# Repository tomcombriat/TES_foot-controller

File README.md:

# TES foot controller

A foot controller performing MIDI looping and arpegiator.
Build instructions and comments will be added in a near future…

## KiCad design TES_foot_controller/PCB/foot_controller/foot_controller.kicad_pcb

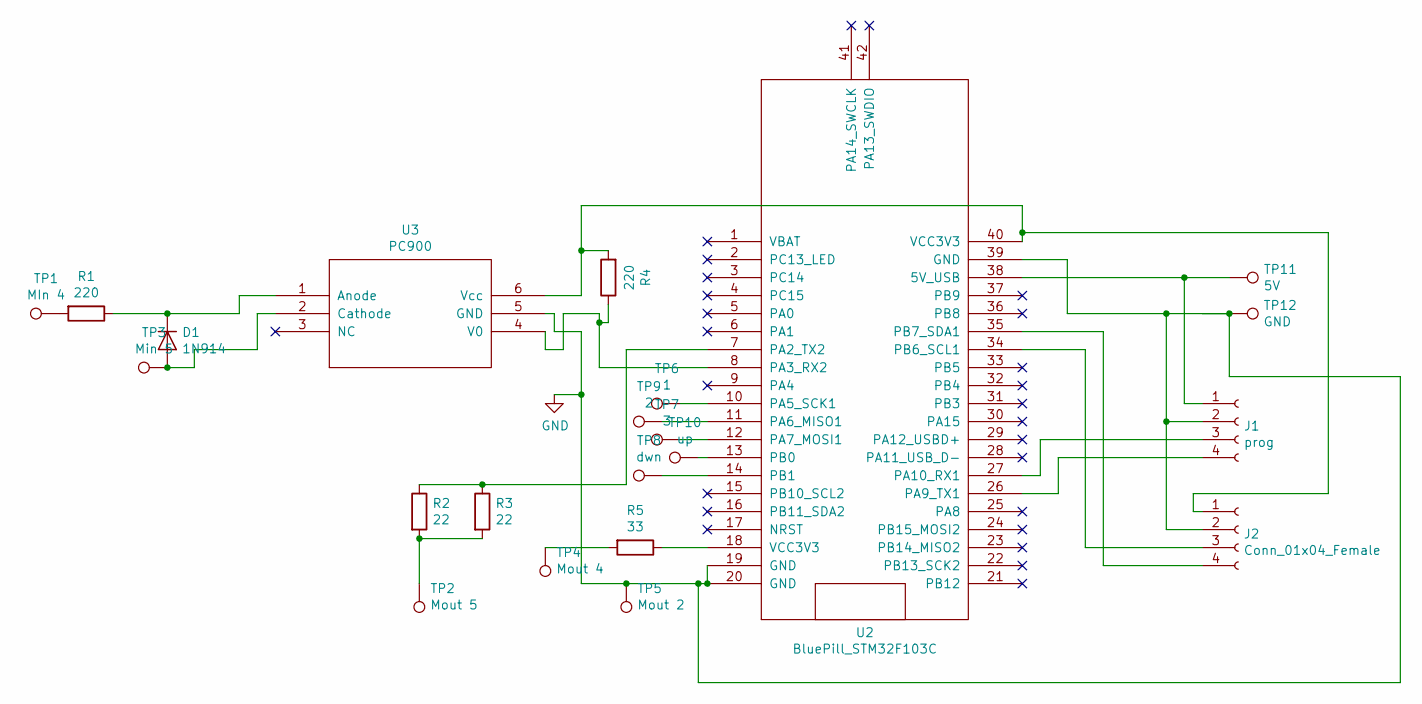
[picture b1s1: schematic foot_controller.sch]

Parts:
D1: 1N914; D_DO-35_SOD27_P7.62mm_Horizontal
J1: prog; PinHeader_1x04_P2.54mm_Vertical
J2: Conn_01x04_Female; PinHeader_1x04_P2.54mm_Vertical
R1, R4: 220; R_Axial_DIN0207_L6.3mm_D2.5mm_P7.62mm_Horizontal
R2, R3: 22; R_Axial_DIN0207_L6.3mm_D2.5mm_P7.62mm_Horizontal
R5: 33; R_Axial_DIN0207_L6.3mm_D2.5mm_P7.62mm_Horizontal
TP1: MIn 4; Pin_D1.2mm_L11.3mm_W3.0mm_Flat
TP2: Mout 5; Pin_D1.2mm_L11.3mm_W3.0mm_Flat
TP3: Min 5; Pin_D1.2mm_L11.3mm_W3.0mm_Flat
TP4: Mout 4; Pin_D1.2mm_L11.3mm_W3.0mm_Flat
TP5: Mout 2; Pin_D1.2mm_L11.3mm_W3.0mm_Flat
TP6: 1; Pin_D1.2mm_L11.3mm_W3.0mm_Flat
TP7: 3; Pin_D1.2mm_L11.3mm_W3.0mm_Flat
TP8: dwn; Pin_D1.2mm_L11.3mm_W3.0mm_Flat
TP9: 2; Pin_D1.2mm_L11.3mm_W3.0mm_Flat
TP10: up; Pin_D1.2mm_L11.3mm_W3.0mm_Flat
TP11: 5V; Pin_D1.2mm_L11.3mm_W3.0mm_Flat
TP12: GND; Pin_D1.2mm_L11.3mm_W3.0mm_Flat
U2: BluePill_STM32F103C
U3: PC900

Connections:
GND: J1.2, J2.2, TP5.1, TP12.1, U2.19 (GND), U2.20 (GND), U2.39 (GND), U3.5 (GND)
unnamed: D1.1 (K), R1.1, U3.1 (Anode)
unnamed: D1.2 (A), TP3.1, U3.2 (Cathode)
unnamed: J1.1, TP11.1, U2.38 (5V_USB)
unnamed: J1.3, U2.27 (PA10_RX1)
unnamed: J1.4, U2.26 (PA9_TX1)
unnamed: J2.1, R4.2, U2.40 (VCC3V3), U3.6 (Vcc)
unnamed: J2.3, U2.34 (PB6_SCL1)
unnamed: J2.4, U2.35 (PB7_SDA1)
unnamed: R1.2, TP1.1
unnamed: R2.1, R3.1, U2.7 (PA2_TX2)
unnamed: R2.2, R3.2, TP2.1
unnamed: R4.1, U2.8 (PA3_RX2), U3.4 (V0)
unnamed: R5.1, U2.18 (VCC3V3)
unnamed: R5.2, TP4.1
unnamed: TP6.1, U2.10 (PA5_SCK1)
unnamed: TP7.1, U2.12 (PA7_MOSI1)
unnamed: TP8.1, U2.14 (PB1)
unnamed: TP9.1, U2.11 (PA6_MISO1)
unnamed: TP10.1, U2.13 (PB0)

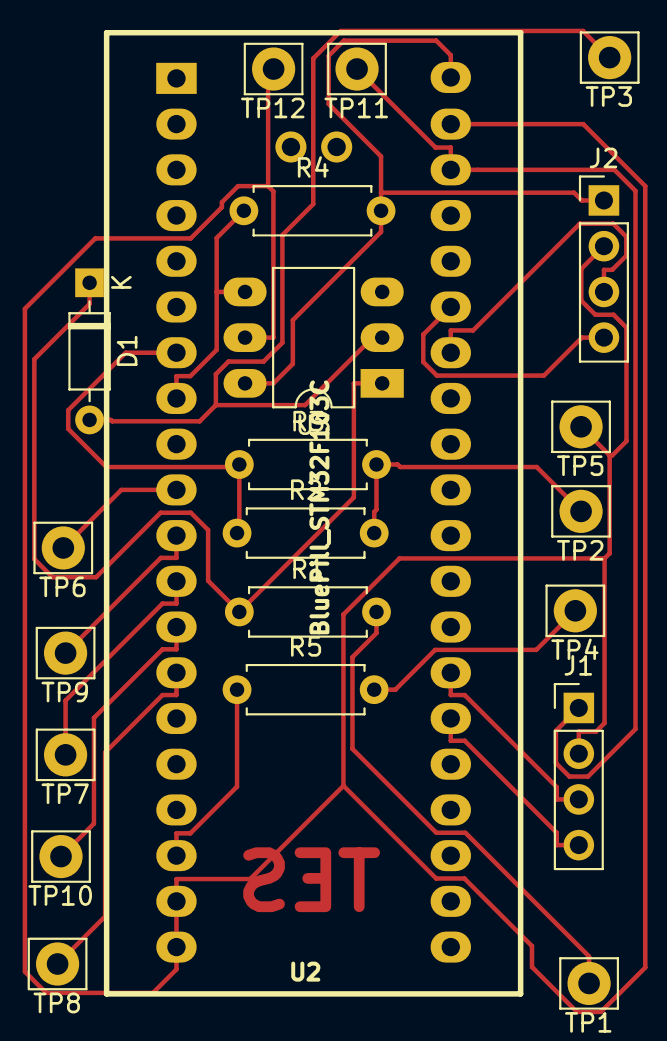
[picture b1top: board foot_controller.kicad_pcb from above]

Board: 2 copper layers, 22 parts (0 on the bottom side), 20 nets.
